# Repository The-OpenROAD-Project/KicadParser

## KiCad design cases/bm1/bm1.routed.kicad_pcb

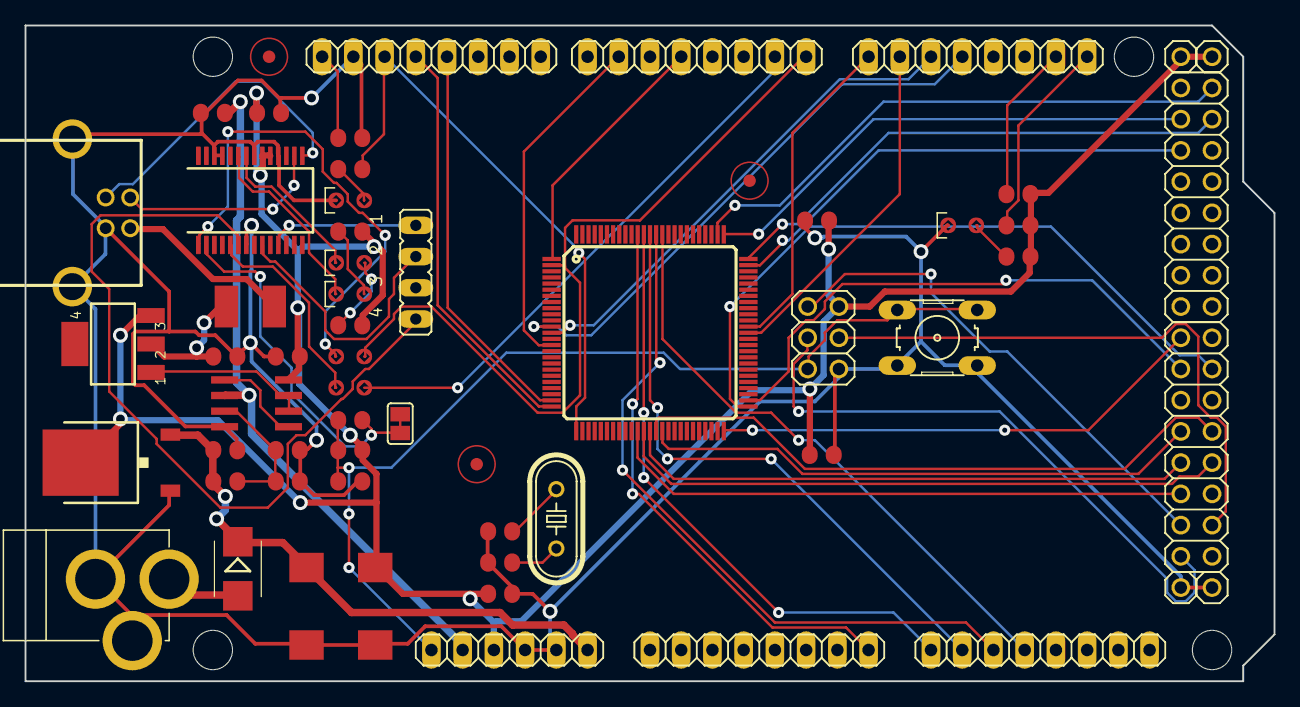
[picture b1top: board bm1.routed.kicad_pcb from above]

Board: 2 copper layers, 101.6 x 53.3 mm, 64 parts (0 on the bottom side), 99 nets.

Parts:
@HOLE0, @HOLE1, @HOLE2, @HOLE3: (no value)
ADCH: 1X08
ADCL: 1X08
C1, C4, C5, C9, C10, C12, C13, C14, C15, C16, C17: 100n; C0805RND
C2, C3, C11: 22p; C0805RND
C6, C7: 100u; SMC_D
COMMUNICATION: 1X08
D1: SMB
F1: 500mA; L1812
IC2: ATMEGA1280-16AU; TQFP100
IC4: MC33269D-5.0; DPACK
IC6: FT232RL; SSOP28
IC7: LM358D; SO08
ICSP: ICSP; 2X03
JP1, JP2: 2X08
JP3, JP4, JP5, JP6: 1X01
L: 0805RND
POWER: 1X06
PWMH: 1X08
PWML: 1X08
PWR: 0805RND
Q2: 16MHz; HC49_S
R1, R8: 1K; R0805RND
R2, R3, R6, R10: 10k; R0805RND
R5: 10K; R0805RND
R7, R9: 1k; R0805RND
R11, R12: 1K; RCL_0805RND
RESET-EN: SJ
RX: 0805RND
S1: B3F-10XX
T1: NDT2955; SOT223
TX: 0805RND
U$1, U$2, U$3: FIDUCIALMOUNT; FIDUCIA-MOUNT
X2: DC21MMX; DC-21MM
X3: JP4
X4: PN61729

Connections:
+3V3: C15.2, IC6.17, IC7.2, POWER.2
+5V: C1.1, C7.+, C9.1, C10.1, C16.1, C17.2, IC2.10, IC2.31, IC2.61, IC2.80, IC2.100, IC4.2, IC6.4, IC6.19, IC6.20, IC7.8, ICSP.2, JP3.1, JP4.1, POWER.3, R2.1, R3.1, R5.2, R7.2, R8.1, R9.2, T1.3
ADC0: ADCL.1, IC2.97
ADC1: ADCL.2, IC2.96
ADC2: ADCL.3, IC2.95
ADC3: ADCL.4, IC2.94
ADC4: ADCL.5, IC2.93
ADC5: ADCL.6, IC2.92
ADC6: ADCL.7, IC2.91
ADC7: ADCL.8, IC2.90
ADC8: ADCH.1, IC2.89
ADC9: ADCH.2, IC2.88
ADC10: ADCH.3, IC2.87
ADC11: ADCH.4, IC2.86
ADC12: ADCH.5, IC2.85
ADC13: ADCH.6, IC2.84
ADC14: ADCH.7, IC2.83
ADC15: ADCH.8, IC2.82
AREF: C4.1, IC2.98, PWMH.8
CMP: C13.2, IC7.3, R6.2, R10.1
CTS: IC6.11, X3.1
D+: IC6.15, X4.3
D-: IC6.16, X4.2
DCD: IC6.10, X3.3
DSR: IC6.9, X3.2
DTR: C12.1, IC6.2, RESET-EN.1, RESET-EN.2
GATE_CMD: IC7.6, IC7.7, T1.1
GND: C1.2, C2.1, C3.1, C4.2, C5.2, C6.-, C7.-, C9.2, C10.2, C11.2, C13.1, C14.2, C15.1, C16.2, C17.1, IC2.11, IC2.32, IC2.62, IC2.81, IC2.99, IC4.1, IC6.7, IC6.18, IC6.21, IC6.25, IC6.26, IC7.4, ICSP.6, JP5.1, JP6.1, L.P$2, POWER.4, POWER.5, PWMH.7, PWR.P$2, R6.1, S1.1, S1.2, X2.1, X2.3, X4.4, X4.P$1, X4.P$2
M8RXD: IC6.1, R11.P$1
M8TXD: IC6.5, R12.P$1
unnamed: L.P$1, R1.2
unnamed: PWR.P$1, R8.2
unnamed: IC7.1, IC7.5
unnamed: C2.2, IC2.34, Q2.1
unnamed: C3.2, IC2.33, Q2.2
unnamed: IC6.23, RX.P$2
unnamed: IC6.22, TX.P$2
unnamed: R7.1, RX.P$1
unnamed: R9.1, TX.P$1
unnamed: F1.2, X4.1
PA0: IC2.78, JP1.16
PA1: IC2.77, JP1.15
PA2: IC2.76, JP1.14
PA3: IC2.75, JP1.13
PA4: IC2.74, JP1.12
PA5: IC2.73, JP1.11
PA6: IC2.72, JP1.10
PA7: IC2.71, JP1.9
PB0: IC2.19, JP2.1
PB1: IC2.20, ICSP.3, JP2.2
PB2: IC2.21, ICSP.4, JP2.3
PB3: IC2.22, ICSP.1, JP2.4
PB4: IC2.23, PWMH.3
PB5: IC2.24, PWMH.4
PB6: IC2.25, PWMH.5
PB7: IC2.26, PWMH.6, R1.1
PC0: IC2.53, JP1.1
PC1: IC2.54, JP1.2
PC2: IC2.55, JP1.3
PC3: IC2.56, JP1.4
PC4: IC2.57, JP1.5
PC5: IC2.58, JP1.6
PC6: IC2.59, JP1.7
PC7: IC2.60, JP1.8
PD7: IC2.50, JP2.16
PE0: IC2.2, PWML.1, R11.P$2
PE1: IC2.3, PWML.2, R12.P$2
PE3: IC2.5, PWML.6
PE4: IC2.6, PWML.3
PE5: IC2.7, PWML.4
PG0: IC2.51, JP2.13
PG1: IC2.52, JP2.14
PG2: IC2.70, JP2.15
PG5: IC2.1, PWML.5
PH3: IC2.15, PWML.7
PH4: IC2.16, PWML.8
PH5: IC2.17, PWMH.1
PH6: IC2.18, PWMH.2
PL0: IC2.35, JP2.5
PL1: IC2.36, JP2.6
PL2: IC2.37, JP2.7
PL3: IC2.38, JP2.8
PL4: IC2.39, JP2.9
PL5: IC2.40, JP2.10
PL6: IC2.41, JP2.11
PL7: IC2.42, JP2.12
PWRIN: D1.A, X2.2
RESET: C11.1, C12.2, IC2.30, ICSP.5, POWER.1, R5.1, S1.3, S1.4
RI: IC6.6, X3.4
RXD1: COMMUNICATION.3, IC2.45
RXD2: COMMUNICATION.5, IC2.12
RXD3: COMMUNICATION.7, IC2.63
SCL: COMMUNICATION.1, IC2.43, R2.2
SDA: COMMUNICATION.2, IC2.44, R3.2
TXD1: COMMUNICATION.4, IC2.46
TXD2: COMMUNICATION.6, IC2.13
TXD3: COMMUNICATION.8, IC2.64
USBVCC: C14.1, F1.1, T1.2
VIN: C5.1, C6.+, D1.C, IC4.3, POWER.6, R10.2

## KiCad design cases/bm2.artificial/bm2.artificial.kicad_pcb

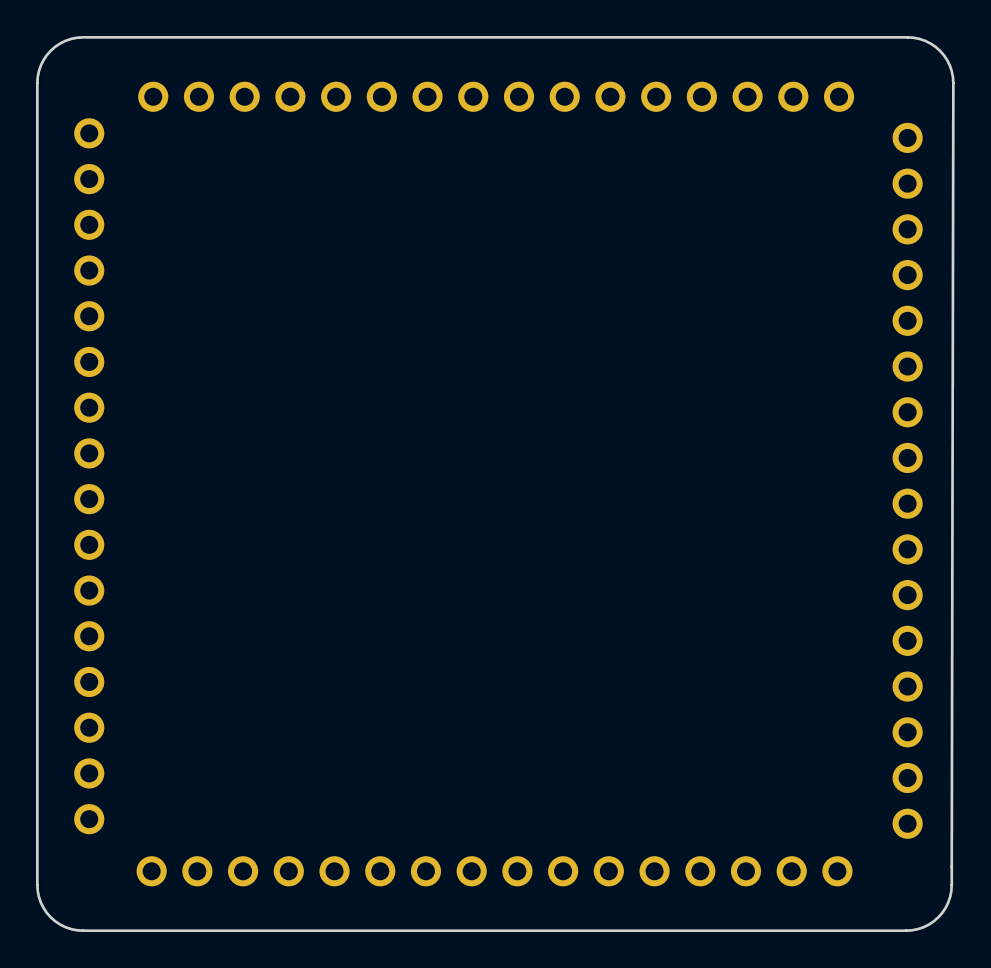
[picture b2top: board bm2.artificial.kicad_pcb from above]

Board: 2 copper layers, 50.9 x 49.6 mm, 4 parts (0 on the bottom side), 12 nets, no tracks yet.

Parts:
JP1, JP2, JP3, JP4: 1X16_ROUND

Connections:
+3V3: JP1.4, JP1.16, JP2.15
A: JP1.7, JP1.15, JP2.12, JP3.5, JP3.12, JP4.11
AREF: JP1.14, JP2.14
B: JP2.11, JP3.2, JP4.2, JP4.7
C: JP2.10, JP3.16
D: JP2.9, JP3.9
E: JP1.12, JP2.8, JP3.14
F: JP1.10, JP2.7, JP3.4
G: JP1.8, JP2.1, JP4.9
GND: JP2.13, JP3.7
MISO: JP1.2, JP2.4, JP4.4
MOSI: JP2.5, JP4.14

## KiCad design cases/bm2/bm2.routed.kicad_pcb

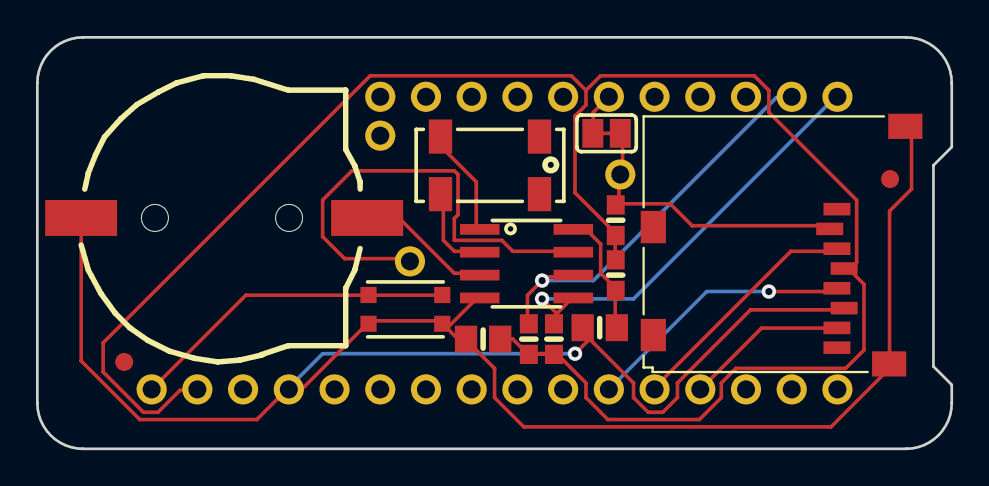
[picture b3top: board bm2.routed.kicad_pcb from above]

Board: 2 copper layers, 50.8 x 22.9 mm, 19 parts (0 on the bottom side), 15 nets.

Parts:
B1: cr1220; CR1220-2
C1, C2: 10uF; 0805-NO
FID1, FID2: FIDUCIAL_1MM
IC1: PCF8523T; SOIC8_150MIL
INT1: 1X01_ROUND
JP1: 1X11_ROUND
JP2: 1X16_ROUND
JP3: 1X01_ROUND
R1, R2: 10K; 0603-NO
R3: 100K; 0603-NO
R4: 1K; 0603-NO
SDCS: 1X01_ROUND
SJ1: SOLDERJUMPER_CLOSEDWIRE
SW1: KMR2; BTN_KMR2_4.6X2.8
X4: microsd; MICROSD
Y1: 32khz; CRYSTAL_8X3.8

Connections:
+3V3: C2.1, JP2.15, R1.2, R2.2, R3.2, R4.1, X4.4
CR1220: B1.+, IC1.3
CS: JP1.6, SJ1.1
GND: B1.-, C1.2, C2.2, IC1.4, JP2.13, SW1.A, SW1.A', X4.6, X4.MT1, X4.MT2
INT1: IC1.7, INT1.1
MISO: JP2.4, X4.7
MOSI: JP2.5, X4.3
unnamed: C1.1, IC1.8, R4.2
unnamed: IC1.1, Y1.P$4
unnamed: IC1.2, Y1.P$1
RESET: JP2.16, SW1.B, SW1.B'
SCK: JP2.6, X4.5
SCL: IC1.6, JP1.10, R2.1
SDA: IC1.5, JP1.11, R1.1
SD_CS: R3.1, SDCS.1, SJ1.2, X4.2

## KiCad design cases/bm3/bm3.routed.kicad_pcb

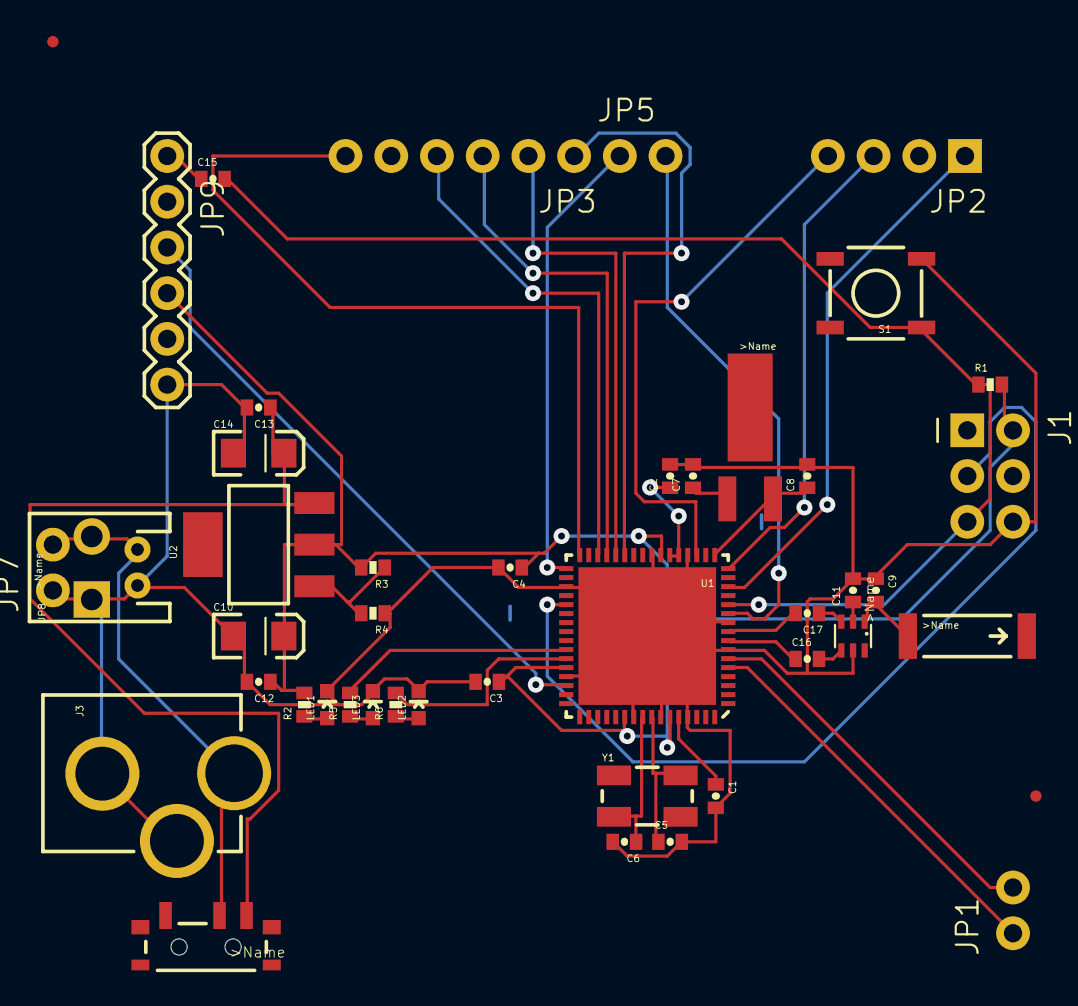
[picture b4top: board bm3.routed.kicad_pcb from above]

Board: 2 copper layers, 48 parts (0 on the bottom side), 41 nets.

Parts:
A1: ANTENNA2SMD5; ANTENNA-CHIP5
B1: 748421245; BALUN
C1, C2, C3, C4, C12: 1uF; 0402-CAP
C5, C6, C7, C8: 12pF; 0402-CAP
C9: 0.75pF; 0402-CAP
C10, C14: 10uF; EIA3216
C11: 22pF; 0402-CAP
C13, C15: 0.1uF; 0402-CAP
C16, C17: JUMP; 0402-CAP
FID1, FID2: FIDUCIALUFIDUCIAL; MICRO-FIDUCIAL
J1: ISP; 2X3-NS
J3: POWER_JACKPTH_LOCK; POWER_JACK_PTH_LOCK
JP1, JP5, JP7: 1X02_NO_SILK
JP2: 1X04_NO_SILK
JP3: 1X06_NS
JP6: JST-2-PTH
JP8: SCREWTERMINAL-3.5MM-2-NS
JP9: FTDI; FTDI_BASIC
LED1: RED; LED-0603
LED2, LED3: GREEN; LED-0603
R1: 10k; 0402-RES
R2: 1k; 0402-RES
R3: 240; 0402-RES
R4: 390; 0402-RES
R5, R6: 330; 0402-RES
S1: TACTILE_SWITCH_SMD
S2: SWITCH-SPST-SMD-A
SJ1, SJ2: SJ_2S-TRACE
U1: ATMEGA128RFA1; QFN-64
U2: LM1117; SOT223
Y1: 16MHz; CRYSTAL-SMD-5X3
Y2: 32.768kHz; CRYSTAL-32KHZ-SMD

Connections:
3.3V: C3.1, C4.1, C10.A, C12.1, J1.2, JP9.VCC, R1.2, R2.2, R3.2, U1.23, U1.34, U1.44, U1.54, U1.59, U2.2
A6: JP1.1, U1.5
A7: JP1.2, U1.6
AVDD: C1.1, U1.60
CLKI: JP5.1, SJ1.2, U1.33
DTR: C15.1, JP9.DTR
DVDD: C2.1, U1.21, U1.22
FB: R3.1, R4.2, U2.1
GND: B1.5, C1.2, C2.2, C3.2, C4.2, C5.2, C6.2, C7.2, C8.2, C9.1, C10.C, C11.2, C12.2, C13.2, C14.C, J1.6, J3.GND, J3.GNDBREAK, JP6.1, JP7.1, JP8.1, JP9.GND, LED1.C, LED2.C, LED3.C, R4.1, S1.3, SJ1.1, SJ2.1, U1.7, U1.10, U1.20, U1.24, U1.35, U1.45, U1.55, U1.58, U1.61, U1.65
unnamed: LED1.A, R2.1
unnamed: C5.1, U1.57, Y1.3
unnamed: C6.1, U1.56, Y1.1
unnamed: C7.1, U1.18, Y2.X1
unnamed: C8.1, U1.17, Y2.X2
unnamed: B1.2, C11.1
unnamed: LED3.A, R5.1
unnamed: J3.PWR, JP6.2, JP7.2, JP8.2, S2.2
unnamed: B1.4, C16.2
unnamed: B1.3, C17.1
unnamed: LED2.A, R6.1
PB6: R5.2, U1.42
PB7: R6.2, U1.43
PD4: JP3.3, U1.29
PD5: JP3.4, U1.30
PD6: JP3.5, U1.31
PD7: JP3.6, U1.32
PG0: JP2.1, U1.14
PG1: JP2.2, U1.15
PG2: JP2.3, U1.16
PG5: JP2.4, U1.19
RESET: C15.2, J1.5, R1.1, S1.1, U1.12
RFANT: A1.FEED, B1.1, C9.2
RFN: C17.2, U1.9
RFP: C16.1, U1.8
RX0: JP9.TXO, U1.46
RX1: JP3.1, U1.27
SCK: J1.3, U1.37
TST: JP5.2, SJ2.2, U1.11
TX0: JP9.RXI, U1.47
TX1: JP3.2, U1.28
VCC: C13.1, C14.A, S2.1, U2.3
